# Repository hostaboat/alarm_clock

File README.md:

# Alarm Clock

## An alarm clock, timer and music player using a Teensy 3.2 and various Adafruit breakout boards.

Many thanks to: 
* **Paul Stoffregen** for the [Teensy 3.2](https://www.pjrc.com/teensy) development board, supporting code base (from which I used as a reference along with the Freescale documentation) and [command line loader](https://github.com/PaulStoffregen/teensy_loader_cli) program which allowed me to develop and test sans the Arduino IDE.
* **Daniel Garcia** for the [FastLED](http://fastled.io) library from which I borrowed.
* [Adafruit](https://www.adafruit.com) for the various breakout boards used.
* [OSH Park](https://oshpark.com) for providing their community PCB service.
* [Othermachine](https://othermachine.co) for the Othermill used to create the enclosure.

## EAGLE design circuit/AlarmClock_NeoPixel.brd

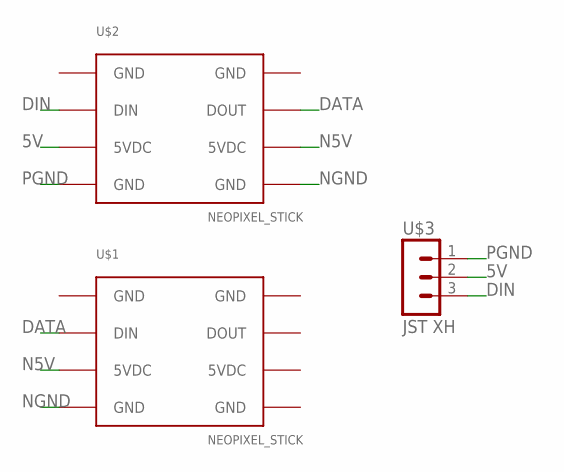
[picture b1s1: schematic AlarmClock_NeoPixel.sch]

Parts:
U$1, U$2: NEOPIXEL_STICK; NEOPIXEL_STICK_SMD_SHORT/HOLES
U$3: JST XH; B3B-XH-A

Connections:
5V: U$2.5VDC@1 (5VDC), U$3.2
5VDC: U$1.5VDC@2 (5VDC)
DATA: U$1.DIN, U$2.DOUT
DIN: U$2.DIN, U$3.3
GND: U$1.GND@1 (GND), U$1.GND@3 (GND), U$1.GND@4 (GND), U$2.GND@1 (GND), U$2.GND@3 (GND)
N5V: U$1.5VDC@1 (5VDC), U$2.5VDC@2 (5VDC)
NGND: U$1.GND@2 (GND), U$2.GND@4 (GND)
PGND: U$2.GND@2 (GND), U$3.1

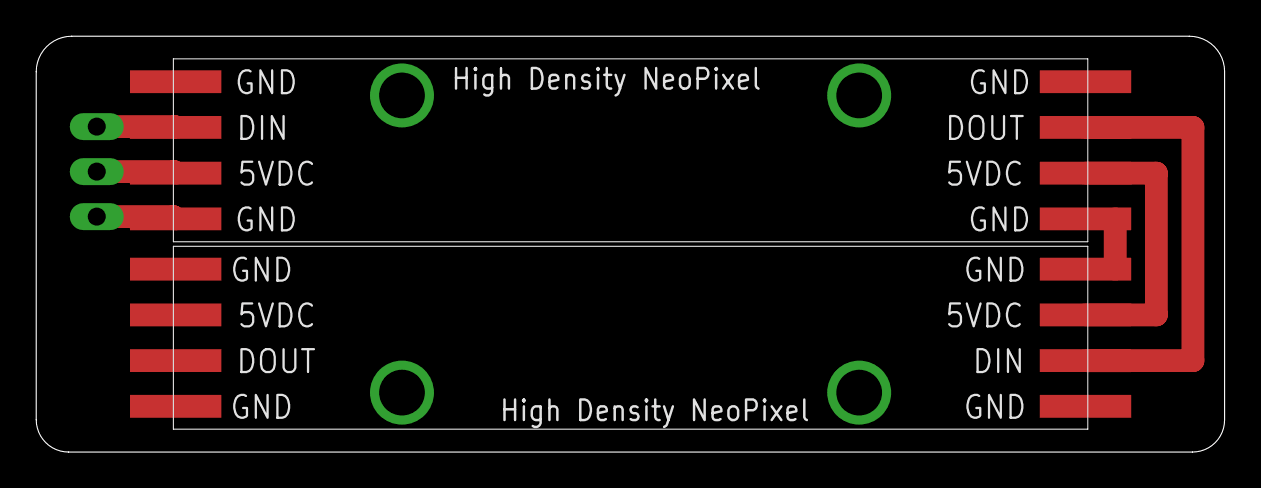
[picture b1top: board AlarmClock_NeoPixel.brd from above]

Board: 2 copper layers, 66.0 x 23.1 mm, 3 parts (1 on the bottom side), 7 nets.

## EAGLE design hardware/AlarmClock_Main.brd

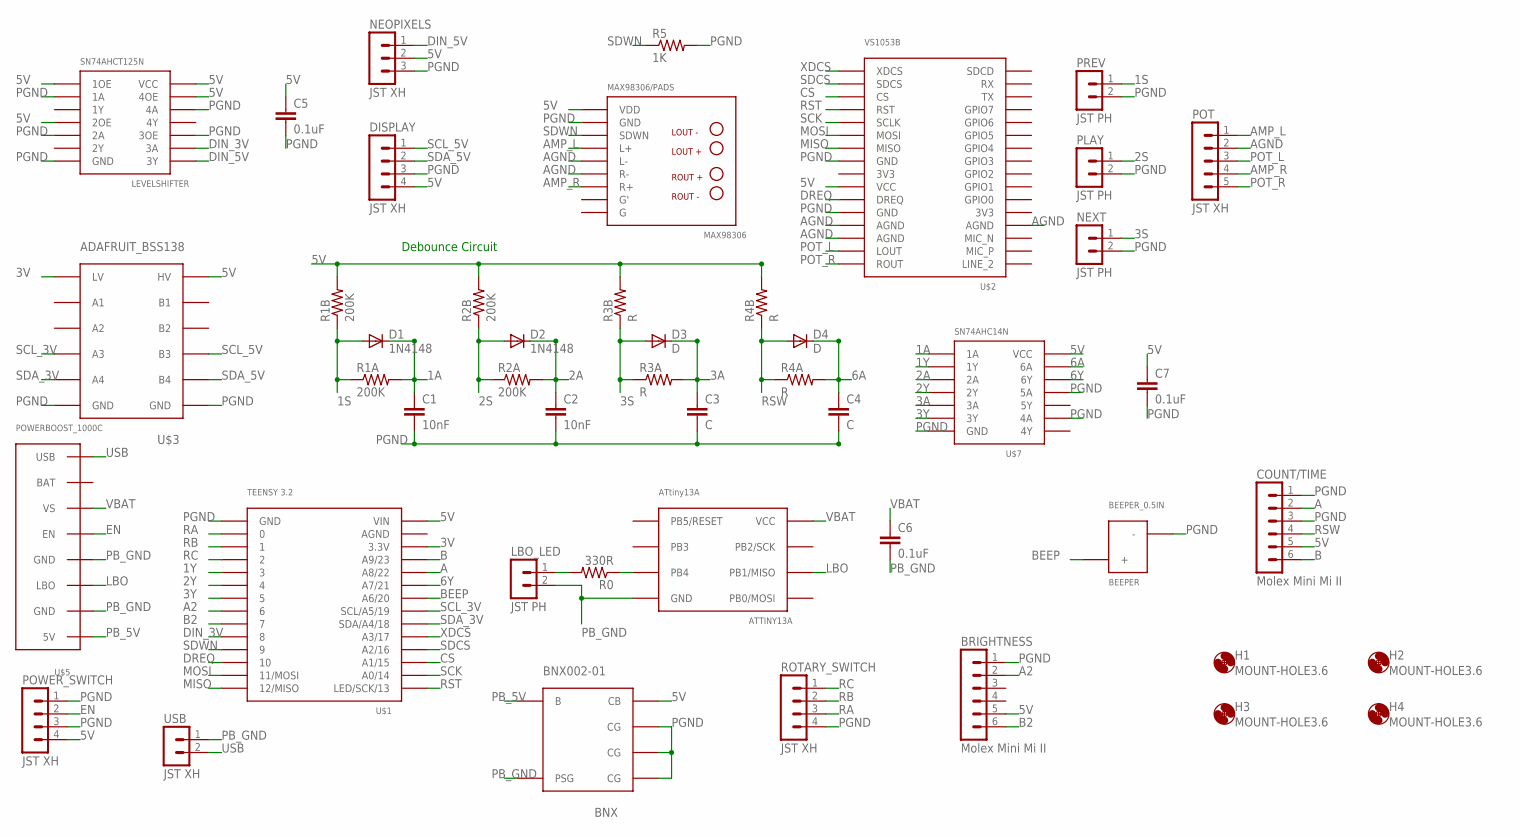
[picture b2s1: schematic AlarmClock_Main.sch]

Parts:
ATTINY13A: ATtiny13A; ATTINY13A
BEEPER: BEEPER_0.5IN
BNX002-01: BNX; BNX002-01
BRIGHTNESS: Molex Mini Mi II; 55447-0670
C1, C2: 10nF; CAPACITOR_0.1IN
C3, C4: C; CAPACITOR_0.1IN
C5, C6, C7: 0.1uF; CAPACITOR_0.1IN
COUNT/TIME: Molex Mini Mi II; 55454-0670
D1, D2: 1N4148
D3, D4: D; 1N4148
DISPLAY: JST XH; B4B-XH-A
H1, H2, H3, H4: MOUNT-HOLE3.6; 3,6
LBO_LED: JST PH; B2B-PH-K-S
LEVELSHIFTER: SN74AHCT125N
MAX98306: MAX98306/PADS; MAX98306
NEOPIXELS: JST XH; B3B-XH-A
NEXT: JST PH; B2B-PH-K-S
PLAY: JST PH; B2B-PH-K-S
POT: JST XH; B5B-XH-A
POWER_SWITCH: JST XH; B4B-XH-A
PREV: JST PH; B2B-PH-K-S
R0: 330R; RESISTOR_0.15IN
R1A, R1B, R2A, R2B: 200K; RESISTOR_0.15IN
R3A, R3B, R4A, R4B: R; RESISTOR_0.15IN
R5: 1K; RESISTOR_0.15IN
ROTARY_SWITCH: JST XH; B4B-XH-A
U$1: TEENSY 3.2; TEENSY-3.1
U$2: VS1053B
U$3: ADAFRUIT_BSS138
U$5: POWERBOOST_1000C
U$7: SN74AHC14N
USB: JST XH; B2B-XH-A

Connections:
1A: C1.P$1 (1), D1.C, R1A.2, U$7.1A
1S: D1.A, PREV.1, R1A.1, R1B.1
1Y: U$1.3, U$7.1Y
2A: C2.P$1 (1), D2.C, R2A.2, U$7.2A
2S: D2.A, PLAY.1, R2A.1, R2B.1
2Y: U$1.4, U$7.2Y
3A: C3.P$1 (1), D3.C, R3A.2, U$7.3A
3S: D3.A, NEXT.1, R3A.1, R3B.1
3V: U$1.3.3V, U$3.LV
3Y: U$1.5, U$7.3Y
5V: BNX002-01.CB, BRIGHTNESS.5, C5.P$1 (1), C7.P$1 (1), COUNT/TIME.5, DISPLAY.4, LEVELSHIFTER.1OE, LEVELSHIFTER.2OE, LEVELSHIFTER.4OE, LEVELSHIFTER.VCC@1 (VCC), MAX98306.VDD@1 (VDD), NEOPIXELS.2, POWER_SWITCH.4, R1B.2, R2B.2, R3B.2, R4B.2, U$1.VIN, U$2.VCC, U$3.HV, U$7.VCC@1 (VCC)
6A: C4.P$1 (1), D4.C, R4A.2, U$7.6A
6Y: U$1.A7/21, U$7.6Y
A: COUNT/TIME.2, U$1.A8/22
A2: BRIGHTNESS.2, U$1.6
AGND: MAX98306.L-, MAX98306.R-, POT.2, U$2.AGND@1 (AGND), U$2.AGND@2 (AGND), U$2.AGND@3 (AGND)
AMP_L: MAX98306.L+, POT.1
AMP_R: MAX98306.R+, POT.4
B: COUNT/TIME.6, U$1.A9/23
B2: BRIGHTNESS.6, U$1.7
BEEP: BEEPER.+, U$1.A6/20
CS: U$1.A1/15, U$2.CS
DIN_3V: LEVELSHIFTER.3A, U$1.8
DIN_5V: LEVELSHIFTER.3Y, NEOPIXELS.1
DREQ: U$1.10, U$2.DREQ
EN: POWER_SWITCH.2, U$5.P$EN (EN)
LBO: ATTINY13A.PB1/MISO, U$5.P$LBO (LBO)
MISO: U$1.12/MISO, U$2.MISO
MOSI: U$1.11/MOSI, U$2.MOSI
unnamed: LBO_LED.1, R0.2
unnamed: ATTINY13A.PB4, R0.1
PB_5V: BNX002-01.B, U$5.P$5V (5V)
PB_GND: ATTINY13A.GND, BNX002-01.PSG, C6.P$2 (2), LBO_LED.2, U$5.P$GND@1 (GND), U$5.P$GND@2 (GND), USB.1
PGND: BEEPER.-, BNX002-01.CG@1 (CG), BNX002-01.CG@2 (CG), BNX002-01.CG@3 (CG), BRIGHTNESS.1, C1.P$2 (2), C2.P$2 (2), C3.P$2 (2), C4.P$2 (2), C5.P$2 (2), C7.P$2 (2), COUNT/TIME.1, COUNT/TIME.3, DISPLAY.3, LEVELSHIFTER.1A, LEVELSHIFTER.2A, LEVELSHIFTER.3OE, LEVELSHIFTER.4A, LEVELSHIFTER.GND@1 (GND), MAX98306.GND@1 (GND), NEOPIXELS.3, NEXT.2, PLAY.2, POWER_SWITCH.1, POWER_SWITCH.3, PREV.2, R5.2, ROTARY_SWITCH.4, U$1.GND, U$2.GND@1 (GND), U$2.GND@2 (GND), U$3.GND@1 (GND), U$3.GND@2 (GND), U$7.4A, U$7.5A, U$7.GND@1 (GND)
POT_L: POT.3, U$2.LOUT
POT_R: POT.5, U$2.ROUT
RA: ROTARY_SWITCH.3, U$1.0
RB: ROTARY_SWITCH.2, U$1.1
RC: ROTARY_SWITCH.1, U$1.2
RST: U$1.LED/SCK/13, U$2.RST
RSW: COUNT/TIME.4, D4.A, R4A.1, R4B.1
SCK: U$1.A0/14, U$2.SCLK
SCL_3V: U$1.SCL/A5/19, U$3.A3
SCL_5V: DISPLAY.1, U$3.B3
SDA_3V: U$1.SDA/A4/18, U$3.A4
SDA_5V: DISPLAY.2, U$3.B4
SDCS: U$1.A2/16, U$2.SDCS
SDWN: MAX98306.SDWN, R5.1, U$1.9
USB: U$5.P$USB (USB), USB.2
VBAT: ATTINY13A.VCC, C6.P$1 (1), U$5.P$VS (VS)
XDCS: U$1.A3/17, U$2.XDCS

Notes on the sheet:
Debounce Circuit

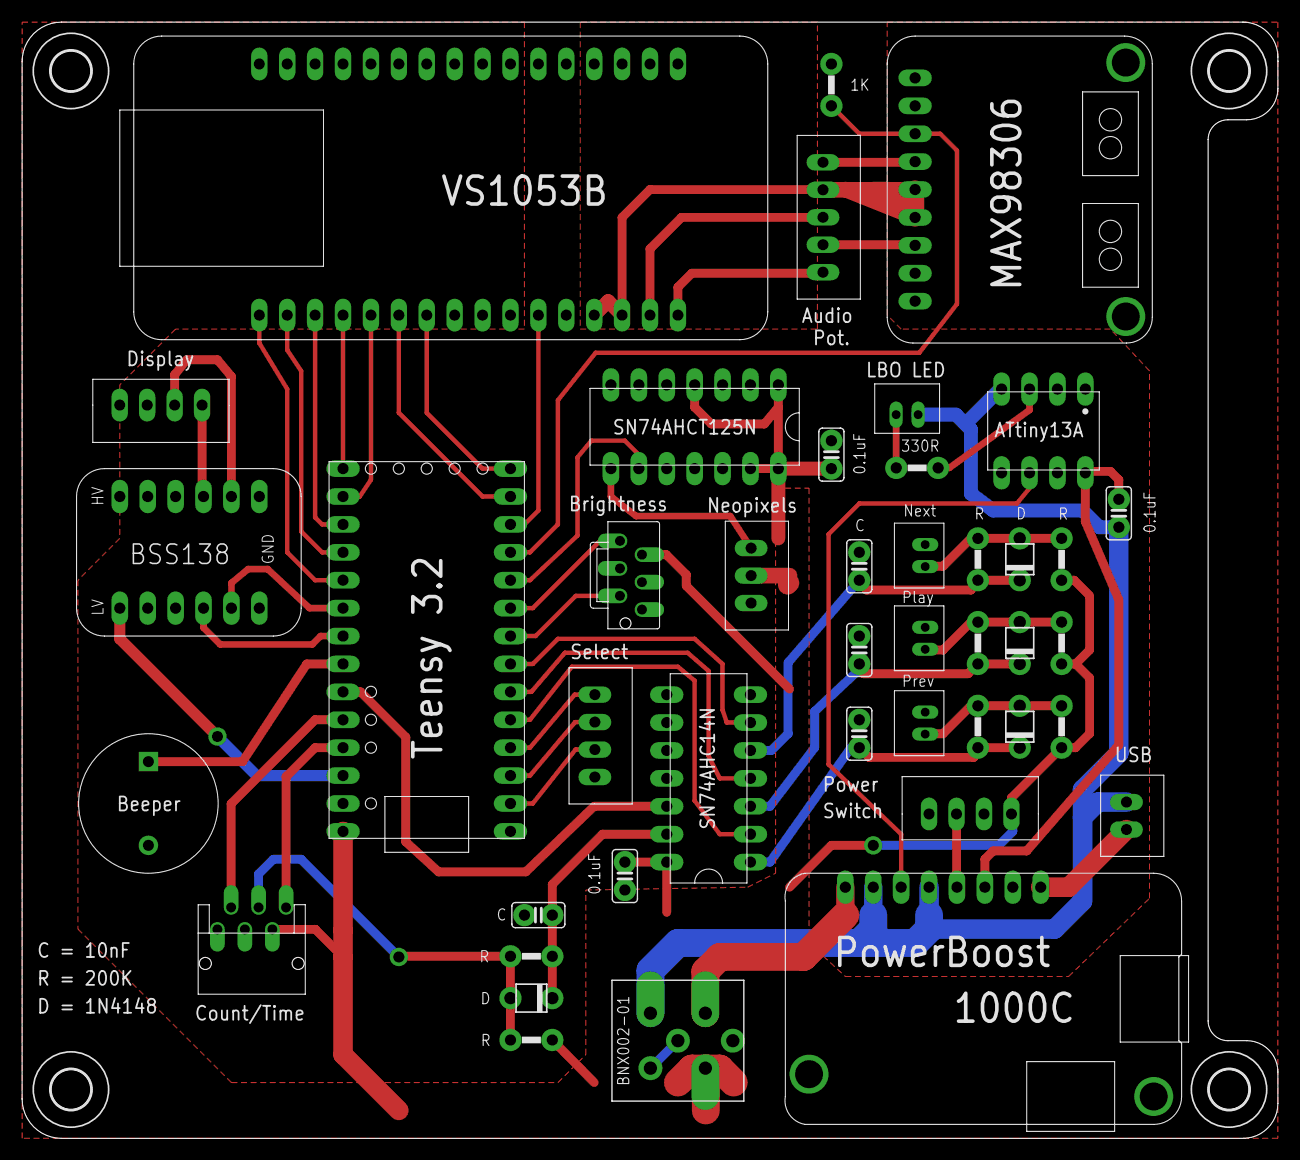
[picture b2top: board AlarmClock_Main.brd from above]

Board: 2 copper layers, 114.3 x 101.6 mm, 47 parts (0 on the bottom side), 51 nets.

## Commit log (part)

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2017-08-16 * Added Reg class to ease getting, setting and clearing bits and fields in a register. Created for use with DMA which has a lot of registers and fields to deal with (though I've currently scrapped th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
2017-08-16 Add ATtiny13A low battery hex file so I don't have to worry about having development environment to compile.
2017-08-21 * Added Daylight Saving Time as a configurable clock option. * For TSI, In addition to waiting while scanning, also wait until End Of Scan fl ag is set.
2017-08-21 Update 7-Segment display brightness to be in sync with LED brightness when going from off to on.
2017-08-24 Display and RTC fixes - Display * Don't automatically turn display on if sleeping or off when showing. Fixes case where brightness is turned down to the point of being off and UI clock update turns i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
2017-08-27 Display, Opti and UI updates - Display * Update to allow string and integer functions to allow displaying from a position for so many digits. * Add an option function for showing a string, colon and 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
2017-08-27 Display and UI updates - Display * Add function to display bars, i.e. underscores, dashes and overscores, and the number of bars starting from the bottom or if reversed starting from the top. * Updat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
2017-08-27 Display fixes * Fix setDashes() and setUnderscores() to blank out any digits not set to a dash or underscore.
2017-08-29 UI, Opti, Pin and Elecmech updates - Opti * Add Palette class and update Leds class to display palettes * Add pseudo-random function rand8() - UI * Add Lighting class to handle night light, timer lig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
2017-08-29 UI Lighting fix * Use member setBrightness in constructor so member _brightness gets set.
2017-08-30 Display, UI, Llwu, Pin, Elecmech and Makefile updates - Display * Change wake() and sleep() methods to take "redisplay" and "clear" parameters, respectively. If sleep(true) then the display will be c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
2017-09-03 Audio, Display, Eeprom, Tsi an UI updates - Audio - DevBeeper * Update stop() to disable toggle. * Override Toggle on() and off() to also check for pin being set. - DevAudio * Remove delay code that 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
2017-09-05 Touch Calibration, Tsi, UI and Elecmech updates - Elecmech * Update evUpdate() to use static_cast so that enums can be passed in. - Tsi * Use interrupt for End of Scan so read() and touched() don't b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
2017-09-05 Lower default Eeprom size to 256.
2017-09-19 Display, Eeprom, Tsi and UI updates - Display * Keep track of last displayed and don't redisplay if new is the same as last. - Eeprom * Use 16-bit writes instead of 32-bit writes to save on space. Pe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
2017-09-19 UI update * Reset _refresh_start to 0 if state changed so uisRefresh() isn't called unnecessarily.
2017-09-19 UI Timer Update * If Player has control of display, call Timer uisWait() if it's in RUNNING or ALERT state so it will alert if it counts down to zero, but just not update display. Do this in pressing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
2017-09-20 UI Touch Fix * Fix uisReset() to exclude TS_OPT and include TS_READ and TS_DONE states and to turn lighting off.
2017-09-23 Display Fix and Display, Eeprom, Llwu, Rtc, Tsi and UI updates - Display * Fix setString() when digit position is not DP_0. * Fix setString() so BL flags are honored when not DF_BL. * Add setOption()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
2017-09-23 UI Timer update * For Timer uisReset() go to set time state if <= WAIT and WAIT otherwise.
2017-09-23 UI updates * Rename Touch class to SetTouch. * Reorganize interface since removal of SetTimer: ------------------------------------------------------ || || MODE || ||---------------------------------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
2017-09-26 UI SetTouch Fixes and Updates - SetTouch uisReset() fixes and uisBegin() / reset() updates * Fix case for TS_READ to go back to initial read state. * Fix case for TS_CONF when it's at TS_CAL_START to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
2017-09-26 Alarm Fix * Rename AS_ON state to AS_WAKE. * Fix "Total Alarm Time" check to be checked in AS_SNOOZE state as well as AS_WAKE. Check was only being done in AS_WAKE state. Should also be checked in AS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
2017-09-29 UI Updates and Fix * Fix to display clock when SL_RESTING and in UIS_CLOCK state. * Add SL_SLEEPING sleep state. * Add reset() member function to Controls. * Consolidate error handling and add beginn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
2017-09-30 UI Updates * Remove Touch class and move touch sensing into Controls class * Remove skip methods from Controls.
2017-10-01 Eeprom, Llwu and UI Updates - Eeprom * Non-templatize read() since it's now only reading 16-bit values. * Change Sleep to Power and have settings for nap, player stop and sleep. - Llwu * Add check fo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
2017-10-01 UI Clock Update * Change show track touch time to 2000 ms. * Reset toggle time if still touched and track not updated.
2017-10-03 UI Timer Fix * Fix Timer to display correctly after nap or sleep.
2017-10-04 UI SetTouch Fix * Tsi is using software triggered scan and read() starts a scan if there isn't a scan already in progress and returns 0 until the end of scan then returns the results of the scan. Bot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
2017-10-04 UI Update * Move SetTouch to rotary switch LEFT / Tertiary mode. * Mode SetPower to rotary switch RIGHT / Secondary mode.
2017-10-07 UI SetTouch Update * Don't reset menu option when resetting state. * Add decimals for abbreviated menu options.
2017-10-10 UI, Display, Opti, Eeprom and Elecmech updates - Display * Add setTimer() and showTimer() methods to Seg7Display that take seconds as an argument. - Eeprom * Update to allow for 3 configurable night 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
2017-10-11 UI Lighting fix * Only turn night light back on from other states if the color isn't black so default color doesn't get activated, since one way besides pressing and holding the encoder switch is to 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
2017-10-12 UI, Display and Opti Updates - Display * Don't treat on/off and awake/sleep as different. If off(), put in STANDBY and on() WAKEUP and ON. Removes unnecessary complication. * Set br_e enum values to 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
2017-10-12 UI update * Reorganize
2017-10-12 UI updates - Timer * Add capability, using touch, to turn the countdown lighting on/off. * Update uisPower() to not sleep, even on touch event, if running or alerting. - Power * Don't need to reset m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
2017-10-15 UI updates * Don't use previously set values when entering Set states but read fresh from Eeprom. * Lower done blink time from 800 to 700 milliseconds. - SetAlarm * Only save on uisEnd() if time was 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
2017-10-15 UI Lighting Fix * Night light animation -> solid color was not toggling from off state and animation was stopping instead of changing to solid color. In toggleAni() shouldn't check if lighting is on,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
2017-10-17 UI Power, Timer, SetTouch and Alarm Fixes * In wakeScreens(), if _brightness == 0, which will happen if user turned brightness knob down to the point of being off before sleep or nap occurred, set br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
2017-10-18 UI Clock, SetPower and Power updates - Controls * In reset(), reset touch values as well as other control values. - SetPower * If a time is 0, meaning it's disabled, show "OFF" instead of 0 in displa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
2017-10-21 UI fixes, SysTick and Rtc updates - SysTick * Change init() to start() and add overloaded start() methods that take no arguments, reload value or reload value and priority as arguments. Use defaults 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
2017-11-12 UI SetAlarm Fix * Make sure hour isn't saved if it was updated, but then alarm is disabled.
2017-11-14 Initial documentation commit.
2017-11-14 UI Update * Make errors "recoverable", i.e. only one error per power cycle is displayed. Makes it so user is made aware of a problem, but can still use the device if problem doesn't render device unu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
2017-11-14 Add troubleshooting.
2017-11-14 Add section to Audio refering to Clock about direct track selection.
2017-11-15 Display Fix * Don't set brightness in constructor to avoid or at least lessen the chance of remnants being displayed.
2017-11-15 Rtc, Eeprom, UI and Makefile Updates - Rtc * Remove clock min year code and max year that was initially used for testing. - Eeprom * Remove clock min year - UI - SetClock * Remove bounds check for mi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
2017-11-15 Docs Update * Add Defaults section to Touch Settings * Remove 300 year span of allowable Year values in Set Clock since it's been removed from the code.
2017-11-15 Add multi-action case to Symbols.
2017-11-15 Formatting...
2017-11-15 Change "Changing" to "Replacing" for Coin Cell Battery.
2017-11-16 Add title page
2017-11-16 Caption updates and some rewording.
2017-11-17 Add "Coded" to title and update some wording.
2017-11-17 Update pdf.
2017-11-17 Add Parts to Appendix
2017-11-18 Use Top macro consistently. Clarify symbols for cycling night light by adding states.
2017-11-18 Add sections to Parts & Materials. Change Component to Application.
2017-11-18 Fix typo. Remove dotted line.
2017-11-18 Remove "activity" since this may imply only control interaction constitutes activity.
2017-11-18 Clarify some wording in Adding Songs.
2017-11-19 UI Clock Update * Allow ShowTrack to Nap
2017-11-21 Add scripts. Wording and formatting updates.
2017-11-21 Update Front SVG and PNG so that arrows heads point toward control so as to be consistent with other images.
2017-11-22 Add bug that I've been unable to reproduce to Troubleshooting section. Clarify a couple of troubleshooting items.
2017-11-23 Fix copy/paste typo. Use module font in a couple of places.
2017-11-27 Audio Update * Make finishing incremental so 32 bytes are sent at a time instead of potentially 4100 bytes at once. Prevents potential UI unresponsiveness between songs. * Do finish() when next song 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
2017-12-04 Alarm Fix * In Alarm constructor, stop Alarm if in progress when device is turned on.
2017-12-09 Add mounting hardware for Display and Lighting.
2017-12-09 Add rubber washers and aluminum holders for Speakers.
2017-12-10 Update number of JST terminal crimps.
2018-02-04 Fix typo. Remove SIM_CLKDIV1_OUTDIV3 since it doesn't exist for this MCU.
2018-03-13 Initial USB Mass Storage Bulk-Only SCSI Command Set support.
2018-03-26 DMA initial commit & updates to Disk, Scsi, Usb and SPI
    TODO: Implement handling of possible errors with DMA and SD
    DMA
    * Added DMA capability
    DevDisk
    * Added methods pure virtual methods open(), read(), write() and close() for
    use with a disk descriptor.
2018-03-28 USB / UI integration * Makefile - Add USB_ENABLED preprocessor flag * DevDisk / DevSD - Add error reporting - Calls to produce() and consume() need not be IRQ protected since both _produced and _cons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
2018-05-01 File fixes * Fix writing more than one cluster. * Move table lookup buffers out of file and into filesystem and better keep track of sector loaded. * Fix EOC check. * Add additional checks for bad in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
2018-05-01 Disk fix * Account for possiblity that a read or write is smaller than the DMA chunk size. If stalled, only resume if canProduce() or canConsume().
2018-05-01 Usb update * Don't make Usb NVIC interrupt higher priority.
2018-05-03 File and String fixes * File - Fix issue where '.' and '..' entries were not being omitted in read(), specifically '..' where the cluster was zero causing the entry to be set free. Properly check and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
2018-05-08 Scsi & Usb update * Handle device USBMS ejection.
2018-05-08 Player update * Don't allow Player to operate while USB connected to avoid potential file corruption and read errors.
2018-05-12 Usb & Scsi updates * Scsi - Change active to initially be false and ejected state as an event. * Usb - Only reset Scsi upon enabling BulkOnlyIface if it hasn't been ejected. - Update connected() stat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
2018-05-12 File & UI update * File - Seperate sorting and writing list of sorted files. * UI - Change reload action in Player to list sorted files since reloading automatically occurs after Usb eject. - Create 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
